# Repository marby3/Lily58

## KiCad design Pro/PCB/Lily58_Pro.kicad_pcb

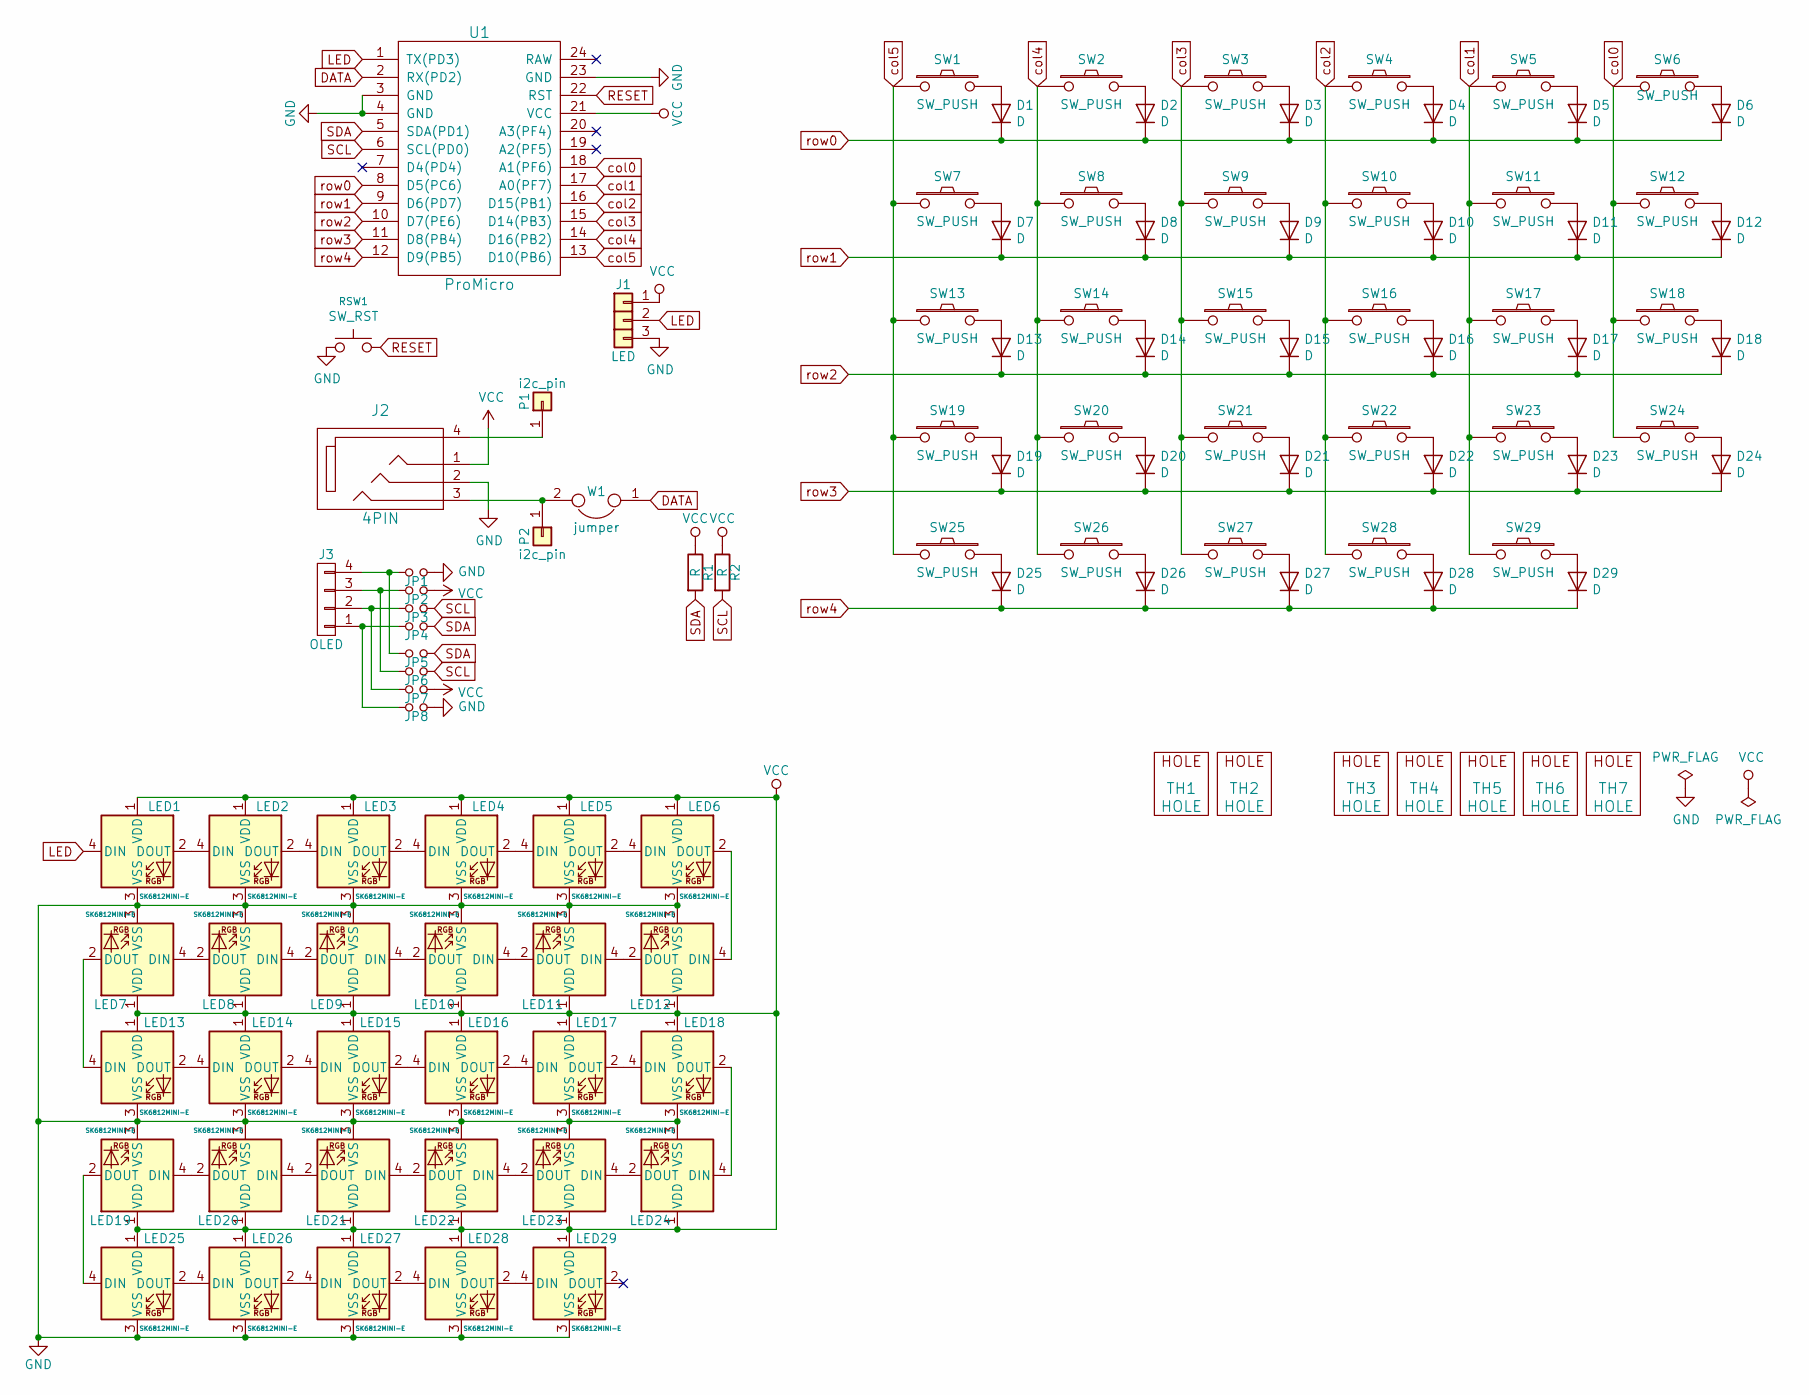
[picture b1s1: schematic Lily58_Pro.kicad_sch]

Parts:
D1, D2, D3, D4, D5, D6, D7, D8, D9, D10, D11, D12, D13, D14, D15, D16, D17, D18, D19, D20, D21, D22, D23, D24, D25, D26, D27, D28, D29: D; D3_TH
J1: LED
J2: 4PIN; MJ-4PP-9
J3: OLED; OLED_4Pin
JP1, JP2, JP3, JP4, JP5, JP6, JP7, JP8: Jumper_NO_Small; Jumper
LED1, LED2, LED3, LED4, LED5, LED6, LED7, LED8, LED9, LED10, LED11, LED12, LED13, LED14, LED15, LED16, LED17, LED18, LED19, LED20, LED21, LED22, LED23, LED24, LED25, LED26, LED27, LED28, LED29: SK6812MINI-E; SK6812MINI-E_both
P1, P2: i2c_pin; 1pin_conn
R1, R2: R; RESISTOR_mini
RSW1: SW_RST; TACT_SWITCH_TVBP06
SW1, SW2, SW3, SW4, SW5, SW6, SW7, SW8, SW9, SW10, SW11, SW12, SW13, SW14, SW15, SW16, SW17, SW18, SW19, SW20, SW21, SW22, SW23, SW24, SW25, SW26, SW27, SW28, SW29: SW_PUSH; Choc_Hotswap_both
TH1, TH2: HOLE; M2_HOLE_PCB
TH3, TH4, TH5, TH6, TH7: HOLE; HOLE_M2_TH
U1: ProMicro; ProMicro_rev2
W1: jumper; jumper_data

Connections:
DATA: U1.2 (RX(PD2)), W1.1
GND: J1.3, J2.2, JP1.2, JP8.2, LED1.3 (VSS), LED2.3 (VSS), LED3.3 (VSS), LED4.3 (VSS), LED5.3 (VSS), LED6.3 (VSS), LED7.3 (VSS), LED8.3 (VSS), LED9.3 (VSS), LED10.3 (VSS), LED11.3 (VSS), LED12.3 (VSS), LED13.3 (VSS), LED14.3 (VSS), LED15.3 (VSS), LED16.3 (VSS), LED17.3 (VSS), LED18.3 (VSS), LED19.3 (VSS), LED20.3 (VSS), LED21.3 (VSS), LED22.3 (VSS), LED23.3 (VSS), LED24.3 (VSS), LED25.3 (VSS), LED26.3 (VSS), LED27.3 (VSS), LED28.3 (VSS), LED29.3 (VSS), RSW1.1, U1.3 (GND), U1.4 (GND), U1.23 (GND)
LED: J1.2, LED1.4 (DIN), U1.1 (TX(PD3))
unnamed: D1.2 (A), SW1.2
unnamed: D2.2 (A), SW2.2
unnamed: D3.2 (A), SW3.2
unnamed: D4.2 (A), SW4.2
unnamed: D5.2 (A), SW5.2
unnamed: D6.2 (A), SW6.2
unnamed: D7.2 (A), SW7.2
unnamed: D8.2 (A), SW8.2
unnamed: D9.2 (A), SW9.2
unnamed: D10.2 (A), SW10.2
unnamed: D11.2 (A), SW11.2
unnamed: D12.2 (A), SW12.2
unnamed: D13.2 (A), SW13.2
unnamed: D14.2 (A), SW14.2
unnamed: D15.2 (A), SW15.2
unnamed: D16.2 (A), SW16.2
unnamed: D17.2 (A), SW17.2
unnamed: D18.2 (A), SW18.2
unnamed: D19.2 (A), SW19.2
unnamed: D20.2 (A), SW20.2
unnamed: D21.2 (A), SW21.2
unnamed: D22.2 (A), SW22.2
unnamed: D23.2 (A), SW23.2
unnamed: D24.2 (A), SW24.2
unnamed: D25.2 (A), SW25.2
unnamed: D26.2 (A), SW26.2
unnamed: D27.2 (A), SW27.2
unnamed: D28.2 (A), SW28.2
unnamed: D29.2 (A), SW29.2
unnamed: J2.3, P2.1, W1.2
unnamed: J2.4, P1.1
unnamed: J3.1, JP4.1, JP8.1
unnamed: J3.2, JP3.1, JP7.1
unnamed: J3.3, JP2.1, JP6.1
unnamed: J3.4, JP1.1, JP5.1
unnamed: LED1.2 (DOUT), LED2.4 (DIN)
unnamed: LED2.2 (DOUT), LED3.4 (DIN)
unnamed: LED3.2 (DOUT), LED4.4 (DIN)
unnamed: LED4.2 (DOUT), LED5.4 (DIN)
unnamed: LED5.2 (DOUT), LED6.4 (DIN)
unnamed: LED7.4 (DIN), LED8.2 (DOUT)
unnamed: LED8.4 (DIN), LED9.2 (DOUT)
unnamed: LED9.4 (DIN), LED10.2 (DOUT)
unnamed: LED10.4 (DIN), LED11.2 (DOUT)
unnamed: LED11.4 (DIN), LED12.2 (DOUT)
unnamed: LED6.2 (DOUT), LED12.4 (DIN)
unnamed: LED13.2 (DOUT), LED14.4 (DIN)
unnamed: LED7.2 (DOUT), LED13.4 (DIN)
unnamed: LED14.2 (DOUT), LED15.4 (DIN)
unnamed: LED15.2 (DOUT), LED16.4 (DIN)
unnamed: LED16.2 (DOUT), LED17.4 (DIN)
unnamed: LED17.2 (DOUT), LED18.4 (DIN)
unnamed: LED18.2 (DOUT), LED24.4 (DIN)
unnamed: LED19.2 (DOUT), LED25.4 (DIN)
unnamed: LED19.4 (DIN), LED20.2 (DOUT)
unnamed: LED20.4 (DIN), LED21.2 (DOUT)
unnamed: LED21.4 (DIN), LED22.2 (DOUT)
unnamed: LED22.4 (DIN), LED23.2 (DOUT)
unnamed: LED23.4 (DIN), LED24.2 (DOUT)
unnamed: LED25.2 (DOUT), LED26.4 (DIN)
unnamed: LED26.2 (DOUT), LED27.4 (DIN)
unnamed: LED27.2 (DOUT), LED28.4 (DIN)
unnamed: LED28.2 (DOUT), LED29.4 (DIN)
RESET: RSW1.2, U1.22 (RST)
SCL: JP3.2, JP6.2, R2.2, U1.6 (SCL(PD0))
SDA: JP4.2, JP5.2, R1.2, U1.5 (SDA(PD1))
VCC: J1.1, J2.1, JP2.2, JP7.2, LED1.1 (VDD), LED2.1 (VDD), LED3.1 (VDD), LED4.1 (VDD), LED5.1 (VDD), LED6.1 (VDD), LED7.1 (VDD), LED8.1 (VDD), LED9.1 (VDD), LED10.1 (VDD), LED11.1 (VDD), LED12.1 (VDD), LED13.1 (VDD), LED14.1 (VDD), LED15.1 (VDD), LED16.1 (VDD), LED17.1 (VDD), LED18.1 (VDD), LED19.1 (VDD), LED20.1 (VDD), LED21.1 (VDD), LED22.1 (VDD), LED23.1 (VDD), LED24.1 (VDD), LED25.1 (VDD), LED26.1 (VDD), LED27.1 (VDD), LED28.1 (VDD), LED29.1 (VDD), R1.1, R2.1, U1.21 (VCC)
col0: SW6.1, SW12.1, SW18.1, SW24.1, U1.18 (A1(PF6))
col1: SW5.1, SW11.1, SW17.1, SW23.1, SW29.1, U1.17 (A0(PF7))
col2: SW4.1, SW10.1, SW16.1, SW22.1, SW28.1, U1.16 (D15(PB1))
col3: SW3.1, SW9.1, SW15.1, SW21.1, SW27.1, U1.15 (D14(PB3))
col4: SW2.1, SW8.1, SW14.1, SW20.1, SW26.1, U1.14 (D16(PB2))
col5: SW1.1, SW7.1, SW13.1, SW19.1, SW25.1, U1.13 (D10(PB6))
row0: D1.1 (K), D2.1 (K), D3.1 (K), D4.1 (K), D5.1 (K), D6.1 (K), U1.8 (D5(PC6))
row1: D7.1 (K), D8.1 (K), D9.1 (K), D10.1 (K), D11.1 (K), D12.1 (K), U1.9 (D6(PD7))
row2: D13.1 (K), D14.1 (K), D15.1 (K), D16.1 (K), D17.1 (K), D18.1 (K), U1.10 (D7(PE6))
row3: D19.1 (K), D20.1 (K), D21.1 (K), D22.1 (K), D23.1 (K), D24.1 (K), U1.11 (D8(PB4))
row4: D25.1 (K), D26.1 (K), D27.1 (K), D28.1 (K), D29.1 (K), U1.12 (D9(PB5))

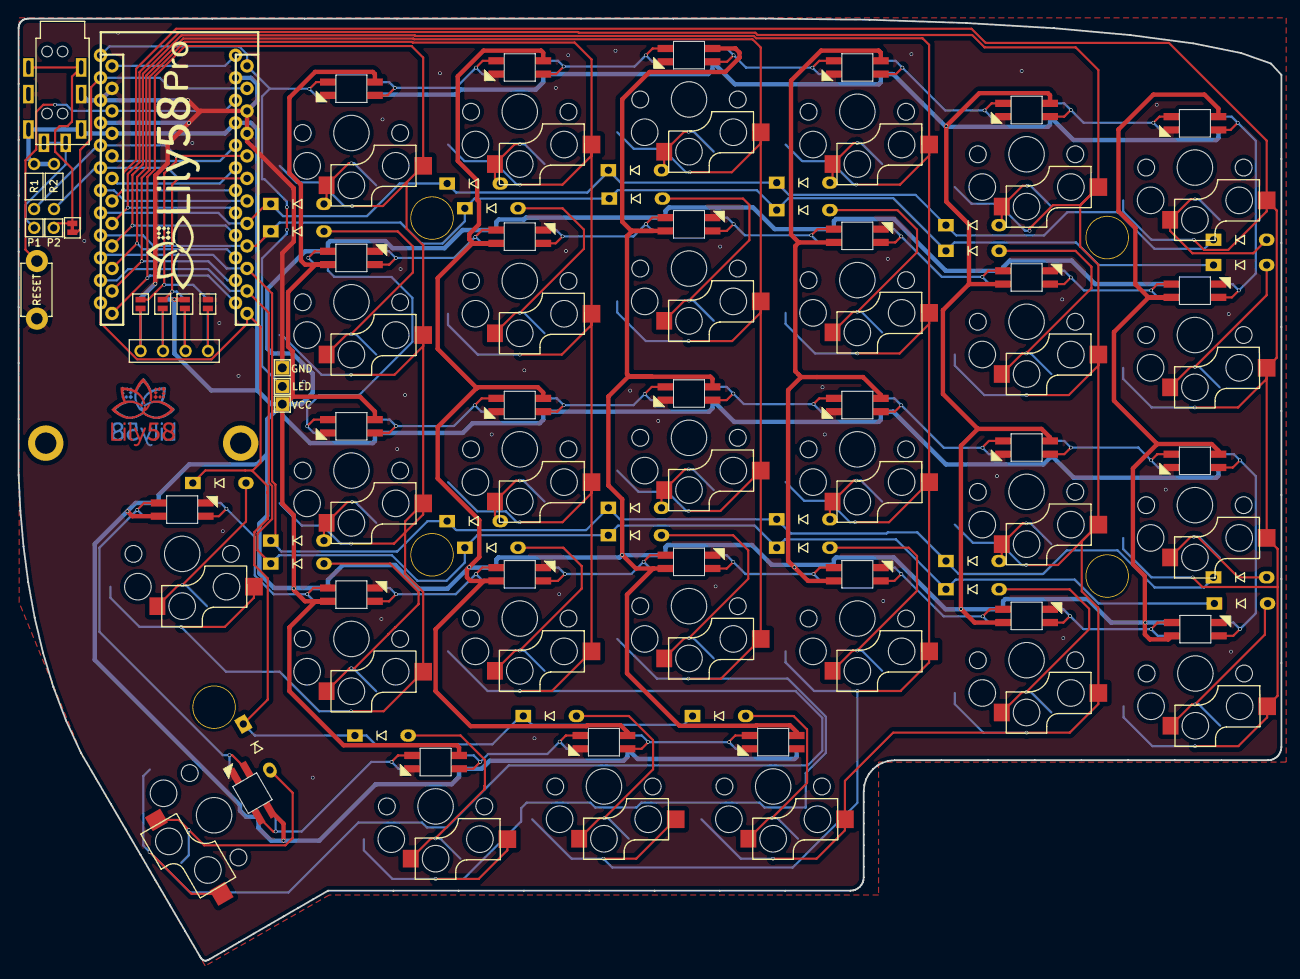
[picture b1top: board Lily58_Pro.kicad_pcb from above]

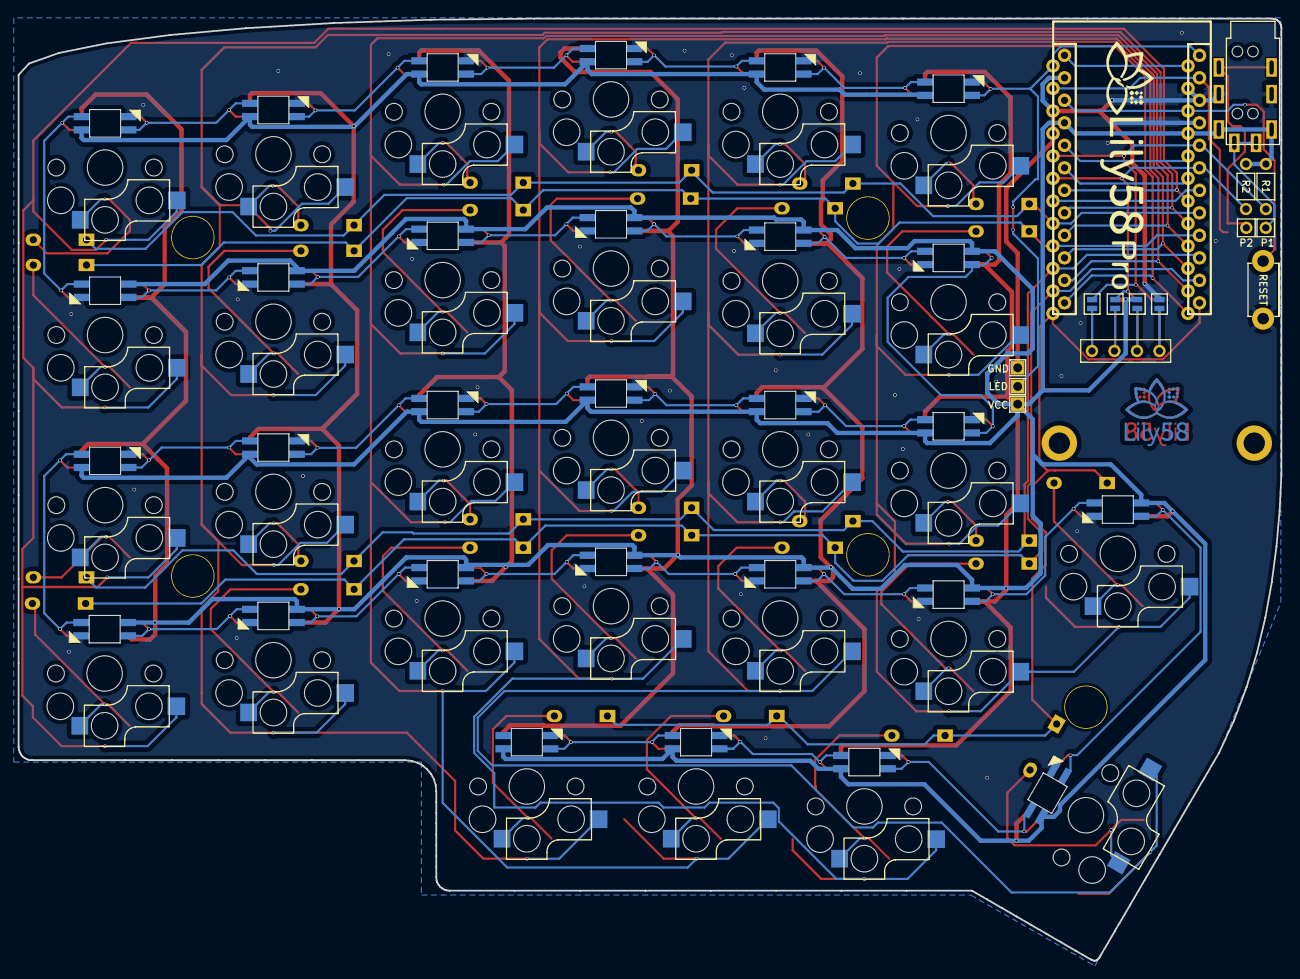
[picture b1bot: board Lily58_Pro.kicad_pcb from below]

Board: 2 copper layers, 142.5 x 106.3 mm, 112 parts (5 on the bottom side), 81 nets.

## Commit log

2022-01-10 Lily58 Choc full backlight edition
